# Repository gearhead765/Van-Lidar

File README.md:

# Van Lidar

## Overview

ESP32 Based app to read a Benewake TF02 Pro Lidar rangefinder and report the distance data via ESP-NOW to the companion Van Level app

## TF02 Pro Configuration

- No sensor configuration should be necessary. We use each sensor's default binary UART mode: 115200 baud, 8N1.  

## Product Images

## Project Structure

```text
├── CAD Model/                       # SolidWorks 3D model of the board and Hammond enclosure
├── Notes/                           # Datasheets and component references
├── Van_Lidar_App/Van_Lidar          # Arduino ESP32 source code
│                 └── data/          # App's LittleFS website
│                     └── images/
├── Van_Lidar_PCB/                   # Kicad board files
│   └── Component Models/            # STEP files of board components
├── HARDWARE.md                      # Hardware specifications and components
├── README.md                        # This file
└── SOFTWARE.md                      # Software description
```

## [Hardware](HARDWARE.md)

## [Software](SOFTWARE.md)

## Features
This application uses an ESP23 to read serial data from a LiDAR rangefinder.  One or two rangefinders can be connected and each will report independently.

The resulting information is presented graphically via a self-hosted webpage and is also made available to the [VanLevel](https://github.com/gearhead765/Van-Level) application using the ESP-Now protocol.  To use ESP-Now, all devices must be on the same WiFi network and channel

The Wifi supports a standard network client, using either DHCP or static network setup, as well as a local Access Point for connecting directly to the device without a local network.

The rangefinder distances can be viewed using any browser that supports Javascript. The webpage displays the current time, the time and value of the latest sensor reading(s), and the time and success/failure of the latest ESP-Now transmission.

## Getting Started

### 1. Hardware Setup
1. Connect the ESP32 board to 12V DC power via connector C1 observing correct polarity.
1. Connect to `VanLidar_nnnn` in your phone or computer's Wi-Fi settings. The `nnnn` suffix is the last four hexadecimal digits of the device's factory MAC address, without colons (for example, `VanLidar_0ABC`).
1. The default password for the access point is `12345678`.
1. You can change the access point name and password in `/setup`. Firmware updates preserve saved AP settings, including the old name if it was saved by earlier firmware.
1. Open the app webpage in any browser by navigating to the hotspot address `192.168.4.1`.
1. Your browser window should look something like this:
<br>

### 2. The Main Display
1. The image above is the standard display in landscape mode.  It will auto rotate for portrait and both views support your browser's `Dark Mode` setting.
1. The browser's current time is displayed along with the latest sensor reading from each sensor and its corresponding reading timestamp.  Below each reading is the status and timestamp of the last ESP-Now message back to the Van_Level app.  With any luck, you should observe all of the various timestamps incrementing.
1.  Finally, at the very bottom of the page, you should see the status of the ESP's WiFi connection.

### 3. AP Configuration
1. To connect the *Van Lidar* app to your local network, or to change the default access point address, name, and/or password, we need to connect to the configuration page.  Navigate your browser to `192.168.4.1/setup`.
1. You will be asked for a login name and password.  These are the same as the AP name and password initially, and can be easily changed later.
<br>
1. After pressing `Sign in`, your browser should now be displaying the app setup page with the `status` tab selected:
<br>
1. On this page, you can change the Access Point name, IP address, and password.
1. If you make changes to any of the AP settings, after hitting `Apply`, you will need to switch to the `Other` tab and select `Reboot` to enable the changes.
1. The setup page authorization name and password **are the same** as the AP name and password.  If you change the AP name and/or password on this page, remember the values so you can log into the device configuration later.
1. There will be an alert at the top of the page if you are using the default name and/or password.  For security reasons, it is best to change these to something uniquely yours.
1. If you forget your AP name or password, you will no longer be able to log into the `setup` page to make changes.  If this happens, you can reset the App to the original defaults by holding down the 'Boot' button on the ESP32 board for 5 seconds while the device reboots.

### 4. Network Configuration
1. The `Network` tab allows you to connect the *Van Lidar* app to your local network.  Pressing the `Scan Wi-Fi` button will search for all available access points.  When the scanning is finished, selecting the `Nearby WLAN` dropdown will present a list of all APs found allowing you to select one.
<br>
1. Enter the WiFi password for this network.
1. You can now select DHCP or Static network configuration.  After you have made your selections and filled in the network password, click `Apply`.  Changes are automatic and you do not need to restart the device.
1. You can switch back to the `Status` tab and verify your selected WiFi connection.

### 5. ESP-Now Receiver

1. Enter the MAC address of the `Van Level` ESP32 controller.  This value can be fount on the Van Level's setup page status tab.  In order for ESP-Now to work correctly, both `Van Level` and `Van Lidar` must be on the same WiFi network and network channel.  Press `Apply` to immediatly use these settings.
2. If the connection to the `Van Level` app is configured correctly, you should see a succesful send message and the send time should be incrementing. 

### 6. Calibration

1. Select the units you wish to use to report the distance values.
1. The `Distance Offset` is useful if the sensor is not mounted at the measurement reference point.
1. Click the `Apply` button to immediately apply these changes.

### 6. Other

1.  `Reboot` will restart the Van Lidar device retaining all of your current settings.
1.  `Reset` will clear your stored Wifi network information and restore the default AP captive portal name and password.  **Make sure** this is what you want before pressing `Reset`.  If you have forgotten your AP name and password and can no longer access the configuration page because of this, it is possible to reset the hardware physically.  This process is discussed in [Software](SOFTWARE.md).
1. Selecting `Update Firmware / File System Upload` will allow *Over The Air* updating of the program and webpages.  See [Software](SOFTWARE.md) for more information on this process.
<br>

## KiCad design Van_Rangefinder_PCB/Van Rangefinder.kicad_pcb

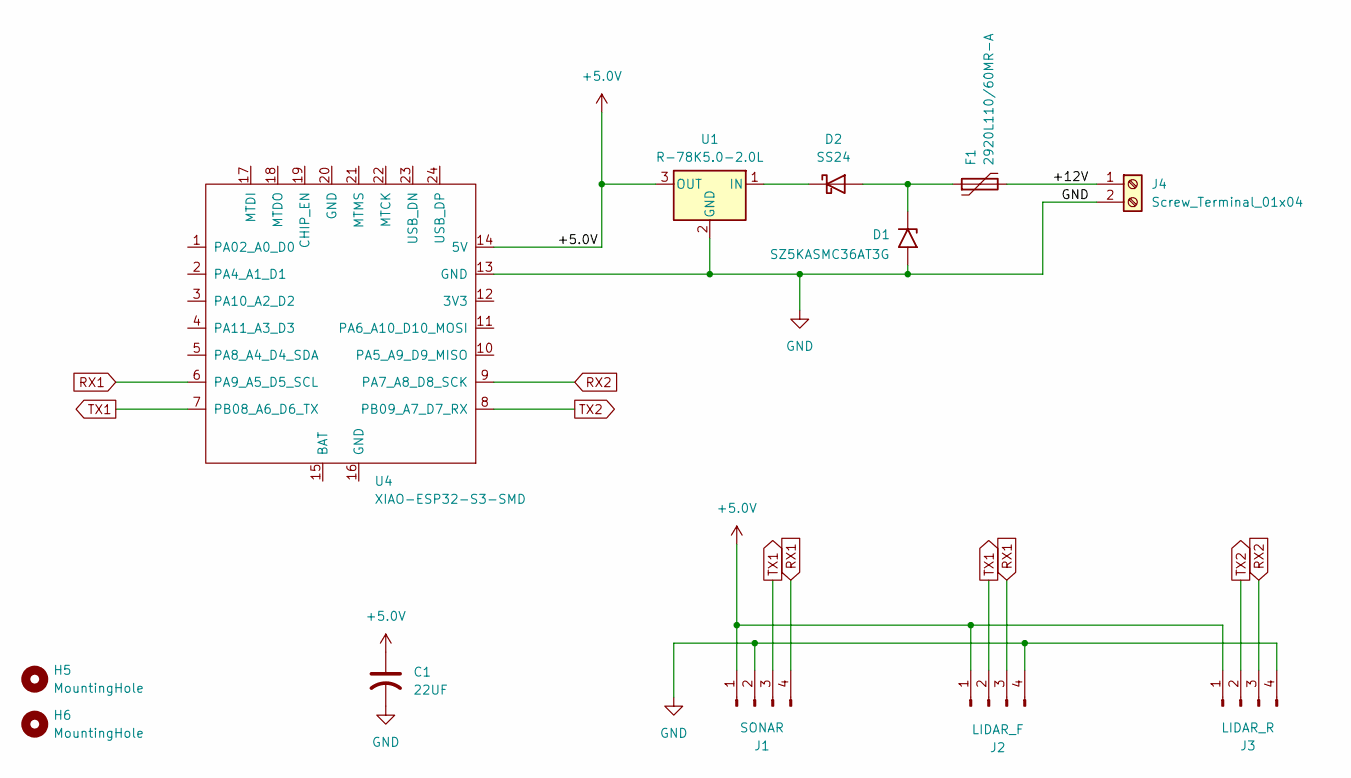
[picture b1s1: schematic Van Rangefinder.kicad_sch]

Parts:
C1: 22UF; C_1210_3225Metric_Pad1.33x2.70mm_HandSolder
D1: SZ5KASMC36AT3G; D_SMC_Handsoldering
D2: SS24; D_SMB_Handsoldering
F1: 2920L110/60MR-A; Fuse_2920_7451Metric_Pad2.10x5.45mm_HandSolder
H5, H6: MountingHole; MountingHole_2.5mm
J1: SONAR; CONN-TH_ZX-HY2.0-4PWZ-Y
J2: LIDAR_F; Molex_PicoBlade_53048-0410_1x04_P1.25mm_Horizontal
J3: LIDAR_R; Molex_PicoBlade_53048-0410_1x04_P1.25mm_Horizontal
J4: Screw_Terminal_01x04; PhoenixContact_MC_1,5_2-G-3.5_1x02_P3.50mm_Horizontal
U1: R-78K5.0-2.0L; Converter_DCDC_RECOM_R-78K-2.0L_THT
U4: XIAO-ESP32-S3-SMD; XIAO-ESP32-S3-SMD-hand

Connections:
+5.0V: C1.1, J1.1, J2.1, J3.1, U1.3 (OUT), U4.14 (5V)
/+12V: F1.2, J4.1
GND: C1.2, D1.2 (A2), J1.2, J2.4, J3.4, J4.2, U1.2 (GND), U4.13 (GND)
unnamed: D1.1 (A1), D2.2 (A), F1.1
unnamed: D2.1 (K), U1.1 (IN)
RX1: J1.4, J2.3, U4.6 (PA9_A5_D5_SCL)
RX2: J3.3, U4.9 (PA7_A8_D8_SCK)
TX1: J1.3, J2.2, U4.7 (PB08_A6_D6_TX)
TX2: J3.2, U4.8 (PB09_A7_D7_RX)

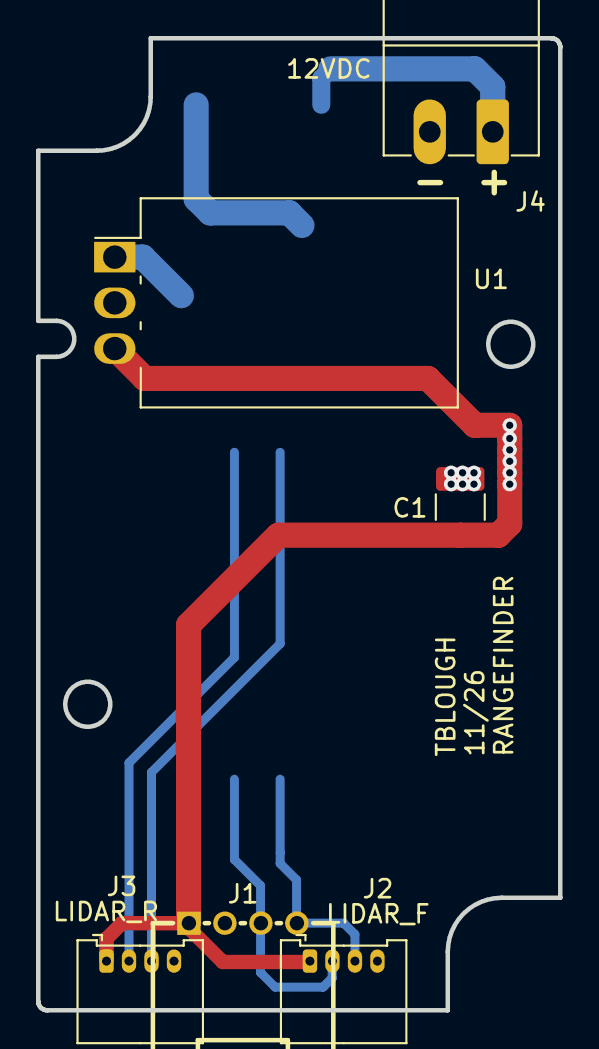
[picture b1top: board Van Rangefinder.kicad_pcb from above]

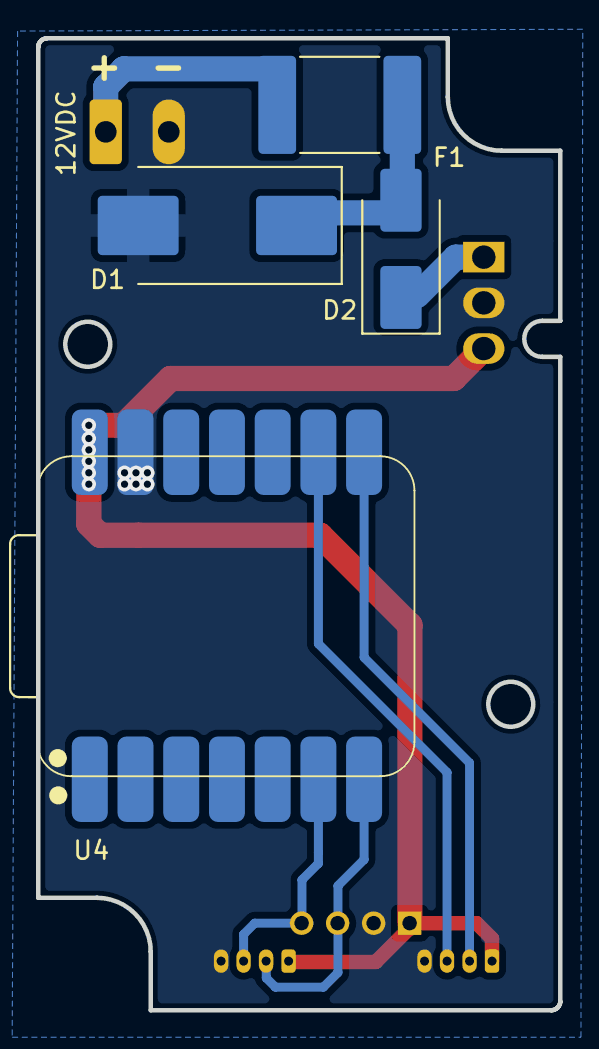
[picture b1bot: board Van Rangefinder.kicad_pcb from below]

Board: 2 copper layers, 29.0 x 54.0 mm, 12 parts (4 on the bottom side), 9 nets.
